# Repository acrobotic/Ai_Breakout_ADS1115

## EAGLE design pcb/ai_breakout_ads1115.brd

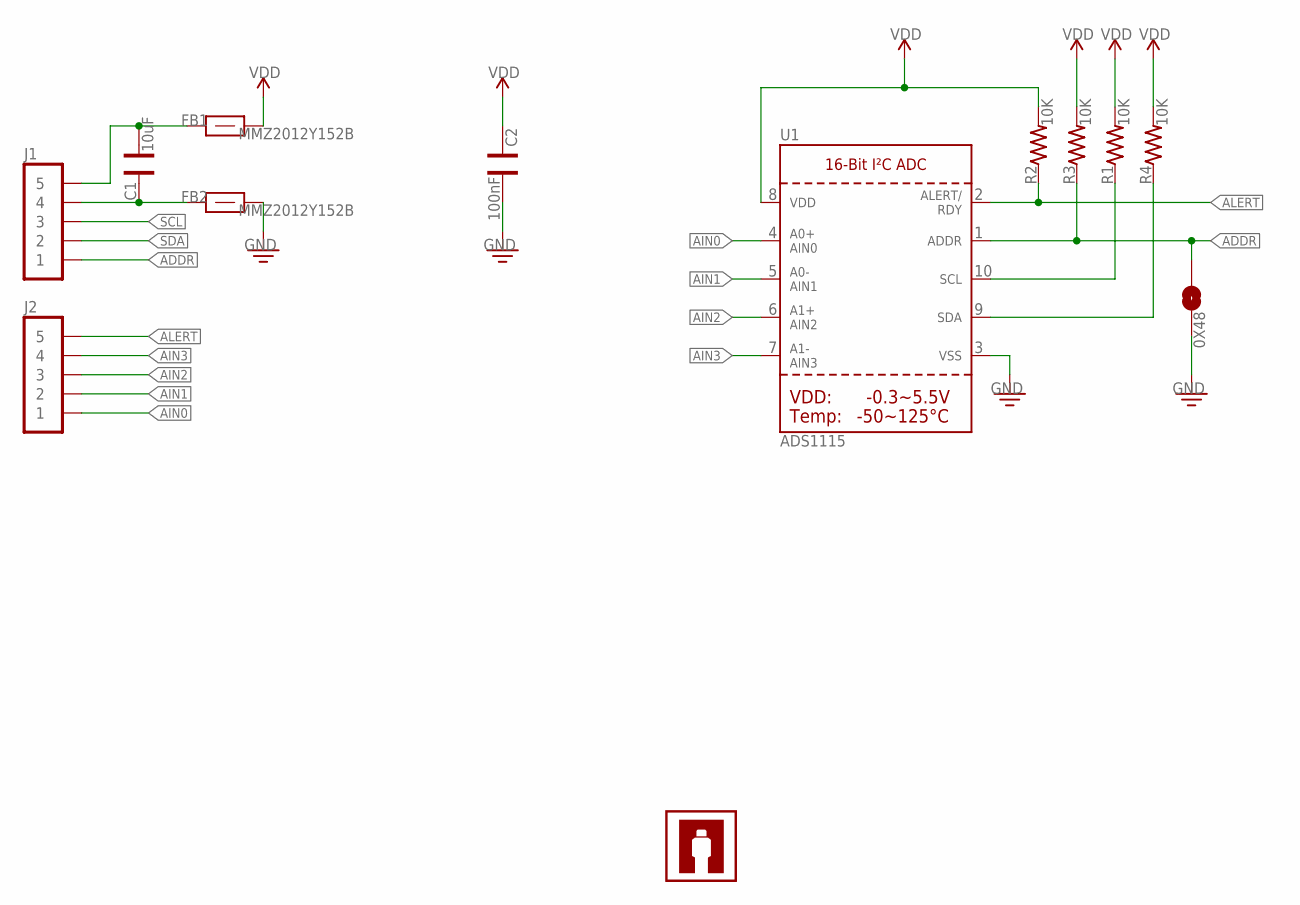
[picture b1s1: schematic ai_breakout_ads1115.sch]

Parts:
0X48: 1X02-SJ-NO
C1: 10uF; CAP-0603
C2: 100nF; CAP-0603
FB1, FB2: MMZ2012Y152B; FB-0603
J1: 1X05
J2: 1X05NOFIRST; 1X05-NOFIRST
R1, R2, R3, R4: 10K; RES-0603
U1: ADS1115; MSOP10
U$2: AI-LOGOXS; AI-LOGO-XS

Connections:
ADDR: 0X48.1, J1.1, R3.1, U1.1 (ADDR)
AIN0: J2.1, U1.4 (AIN0)
AIN1: J2.2, U1.5 (AIN1)
AIN2: J2.3, U1.6 (AIN2)
AIN3: J2.4, U1.7 (AIN3)
ALERT: J2.5, R2.1, U1.2 (ALERT/RDY)
GND: 0X48.2, C2.1, FB2.2, U1.3 (VSS)
unnamed: C1.1, FB1.1, J1.5
unnamed: C1.2, FB2.1, J1.4
SCL: J1.3, R1.1, U1.10 (SCL)
SDA: J1.2, R4.1, U1.9 (SDA)
VDD: C2.2, FB1.2, R1.2, R2.2, R3.2, R4.2, U1.8 (VDD)

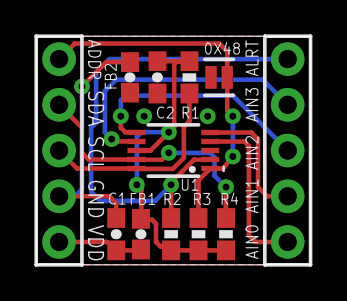
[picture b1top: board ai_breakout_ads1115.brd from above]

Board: 2 copper layers, 15.2 x 12.7 mm, 13 parts (1 on the bottom side), 12 nets.

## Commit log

2015-05-27 routed
2015-05-31 major changes
2015-06-02 minor fix for silkscreen
